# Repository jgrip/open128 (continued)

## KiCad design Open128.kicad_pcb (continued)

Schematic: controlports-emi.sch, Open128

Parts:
EMI1, EMI2, EMI9, EMI10, EMI11: 47 pF; EMI-Filter; Mouser Part 652-EMI470T-RC
EMI3, EMI4, EMI5, EMI6, EMI12, EMI13, EMI14, EMI15, EMI69: 100 pF; EMI-Filter; Mouser Part 81-DSS1NB32A101Q91A

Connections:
/I/O/COL0: EMI11.3; also elsewhere on the board
/I/O/COL1: EMI12.3; also elsewhere on the board
/I/O/COL2: EMI13.3; also elsewhere on the board
/I/O/COL3: EMI14.3; also elsewhere on the board
/I/O/COL4: EMI15.3; also elsewhere on the board
/I/O/Control Ports/Control Ports-EMI/IN_FBTNA: EMI69.1; also elsewhere on the board
/I/O/Control Ports/Control Ports-EMI/IN_FBTNB: EMI15.1; also elsewhere on the board
/I/O/Control Ports/Control Ports-EMI/IN_JOYA0: EMI3.1; also elsewhere on the board
/I/O/Control Ports/Control Ports-EMI/IN_JOYA1: EMI4.1; also elsewhere on the board
/I/O/Control Ports/Control Ports-EMI/IN_JOYA2: EMI5.1; also elsewhere on the board
/I/O/Control Ports/Control Ports-EMI/IN_JOYA3: EMI6.1; also elsewhere on the board
/I/O/Control Ports/Control Ports-EMI/IN_JOYB0: EMI11.1; also elsewhere on the board
/I/O/Control Ports/Control Ports-EMI/IN_JOYB1: EMI12.1; also elsewhere on the board
/I/O/Control Ports/Control Ports-EMI/IN_JOYB2: EMI13.1; also elsewhere on the board
/I/O/Control Ports/Control Ports-EMI/IN_JOYB3: EMI14.1; also elsewhere on the board
/I/O/Control Ports/Control Ports-EMI/IN_POTAX: EMI1.1; also elsewhere on the board
/I/O/Control Ports/Control Ports-EMI/IN_POTAY: EMI2.1; also elsewhere on the board
/I/O/Control Ports/Control Ports-EMI/IN_POTBX: EMI9.1; also elsewhere on the board
/I/O/Control Ports/Control Ports-EMI/IN_POTBY: EMI10.1; also elsewhere on the board
/I/O/Control Ports/Control Ports-EMI/OUT_POTAX: EMI1.3; also elsewhere on the board
/I/O/Control Ports/Control Ports-EMI/OUT_POTAY: EMI2.3; also elsewhere on the board
/I/O/Control Ports/Control Ports-EMI/OUT_POTBX: EMI9.3; also elsewhere on the board
/I/O/Control Ports/Control Ports-EMI/OUT_POTBY: EMI10.3; also elsewhere on the board
/I/O/ROW0: EMI3.3; also elsewhere on the board
/I/O/ROW1: EMI4.3; also elsewhere on the board
/I/O/ROW2: EMI5.3; also elsewhere on the board
/I/O/ROW3: EMI6.3; also elsewhere on the board
/VIC/~LIGHTPEN: EMI69.3; also elsewhere on the board
GND: EMI1.2, EMI2.2, EMI3.2, EMI4.2, EMI5.2, EMI6.2, EMI9.2, EMI10.2, EMI11.2, EMI12.2, EMI13.2, EMI14.2, EMI15.2, EMI69.2; also elsewhere on the board

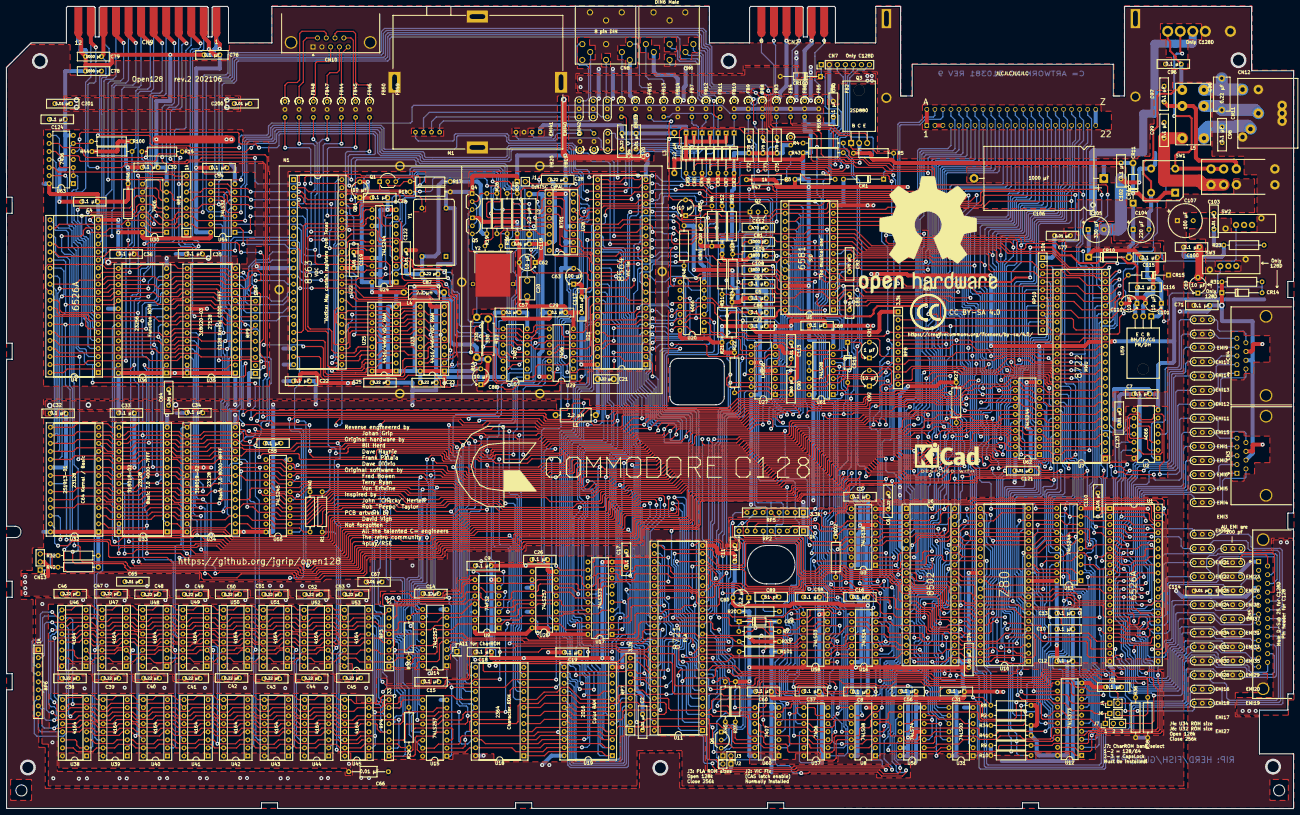
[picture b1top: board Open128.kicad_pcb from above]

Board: 2 copper layers, 406.6 x 253.4 mm, 367 parts (1 on the bottom side), 400 nets.

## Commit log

2021-03-22 Remove cruft and update readme
2021-03-22 Add notice about board not tested yet
2021-03-22 Add image
2021-03-22 Actually fix the image...
2021-03-22 Add PDF schematic and gerber files
2021-06-22 Fix R47/R101
2021-08-06 Update README.md
    Add license badge
2021-09-17 Clean up schematic
2021-09-17 Updated PDF to matched cleaned schematic
2021-09-17 Backlink to CADLAB.io has been added.
2025-05-17 Migrating
